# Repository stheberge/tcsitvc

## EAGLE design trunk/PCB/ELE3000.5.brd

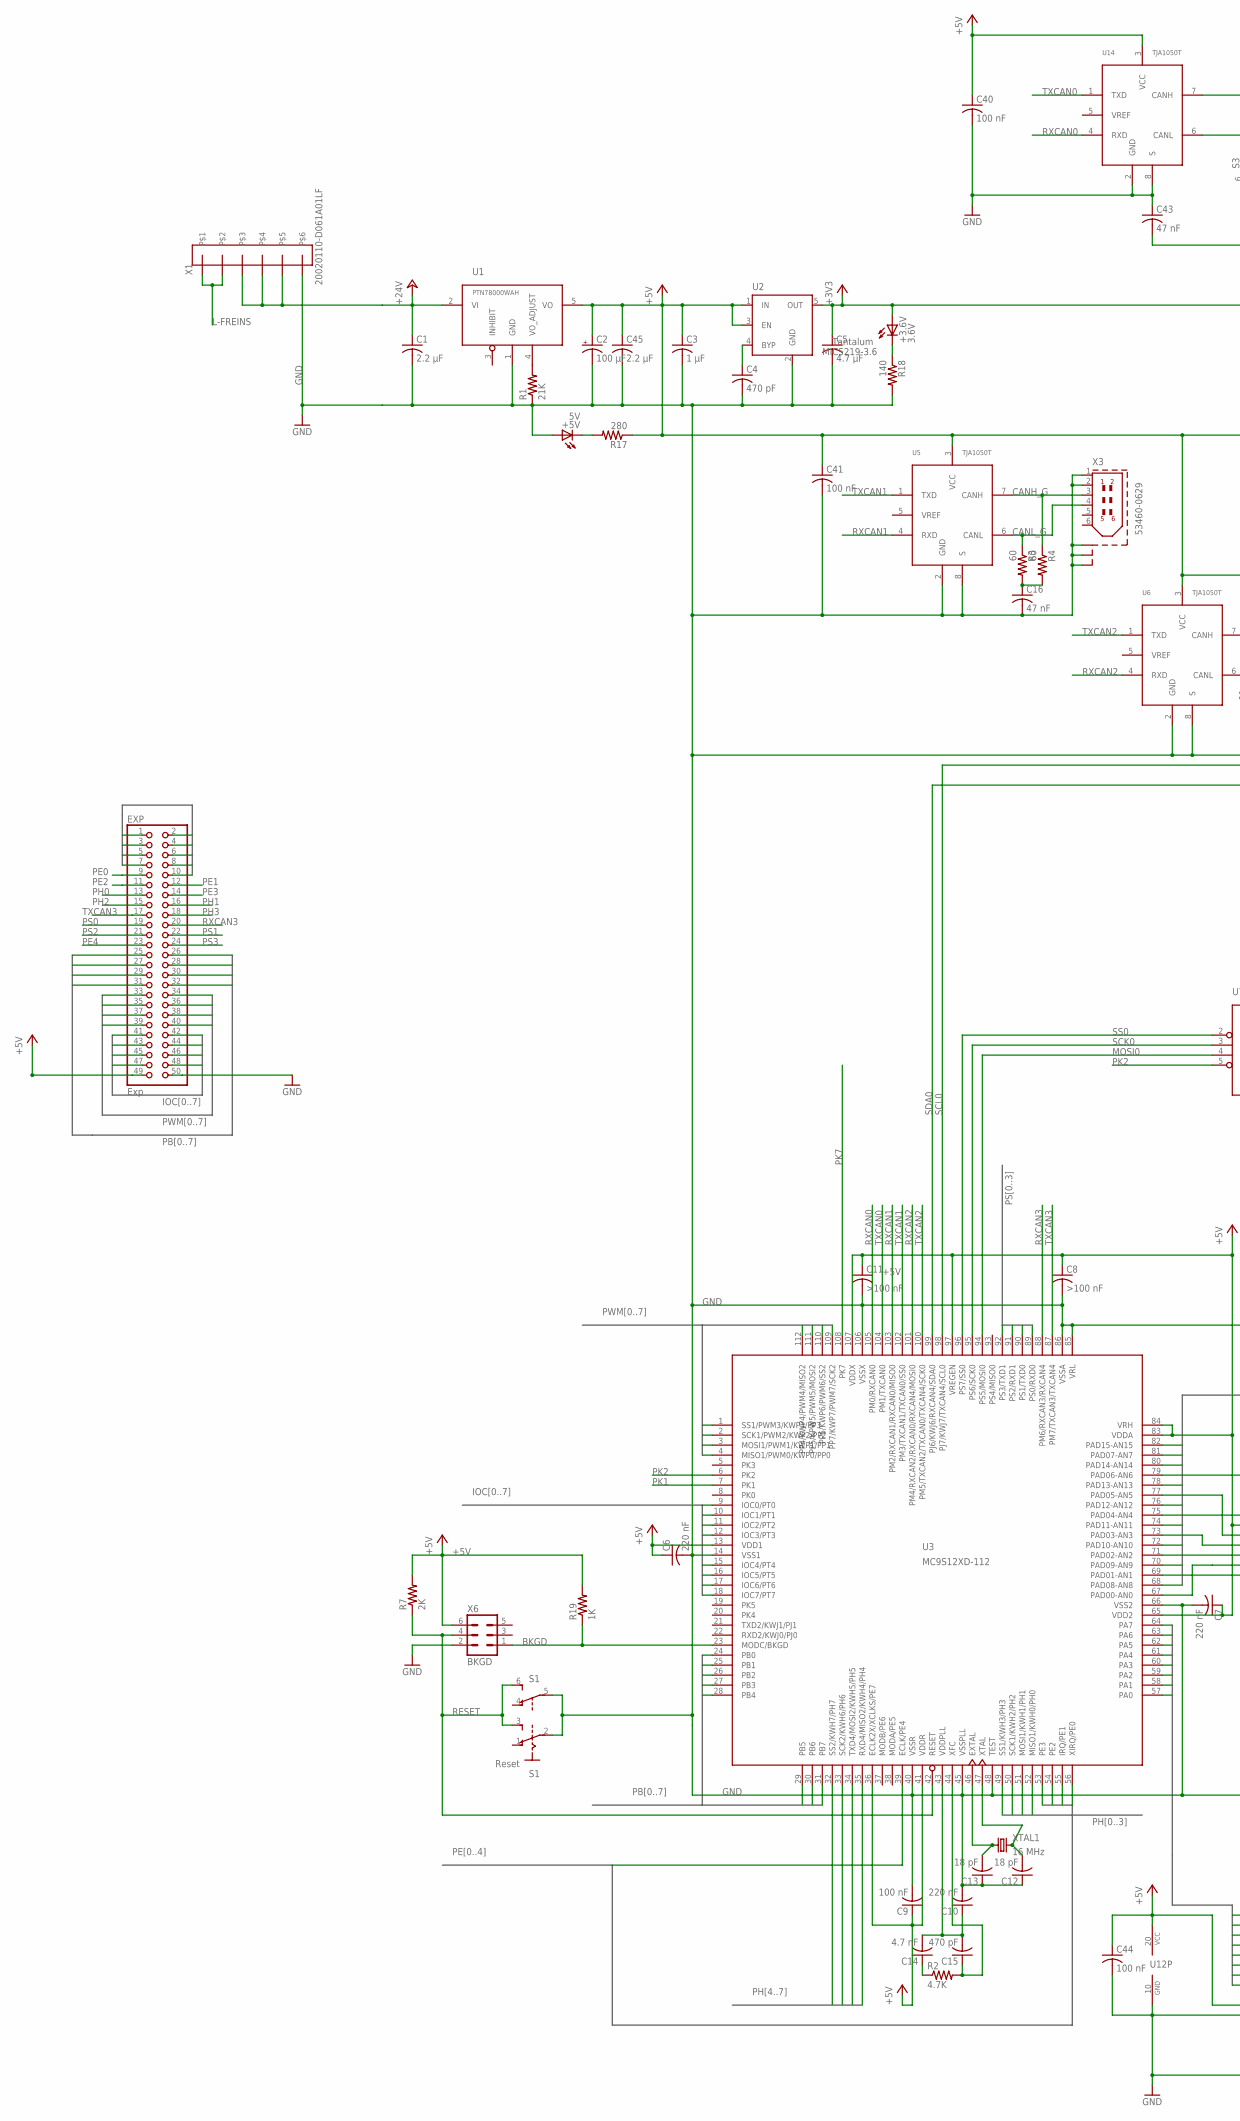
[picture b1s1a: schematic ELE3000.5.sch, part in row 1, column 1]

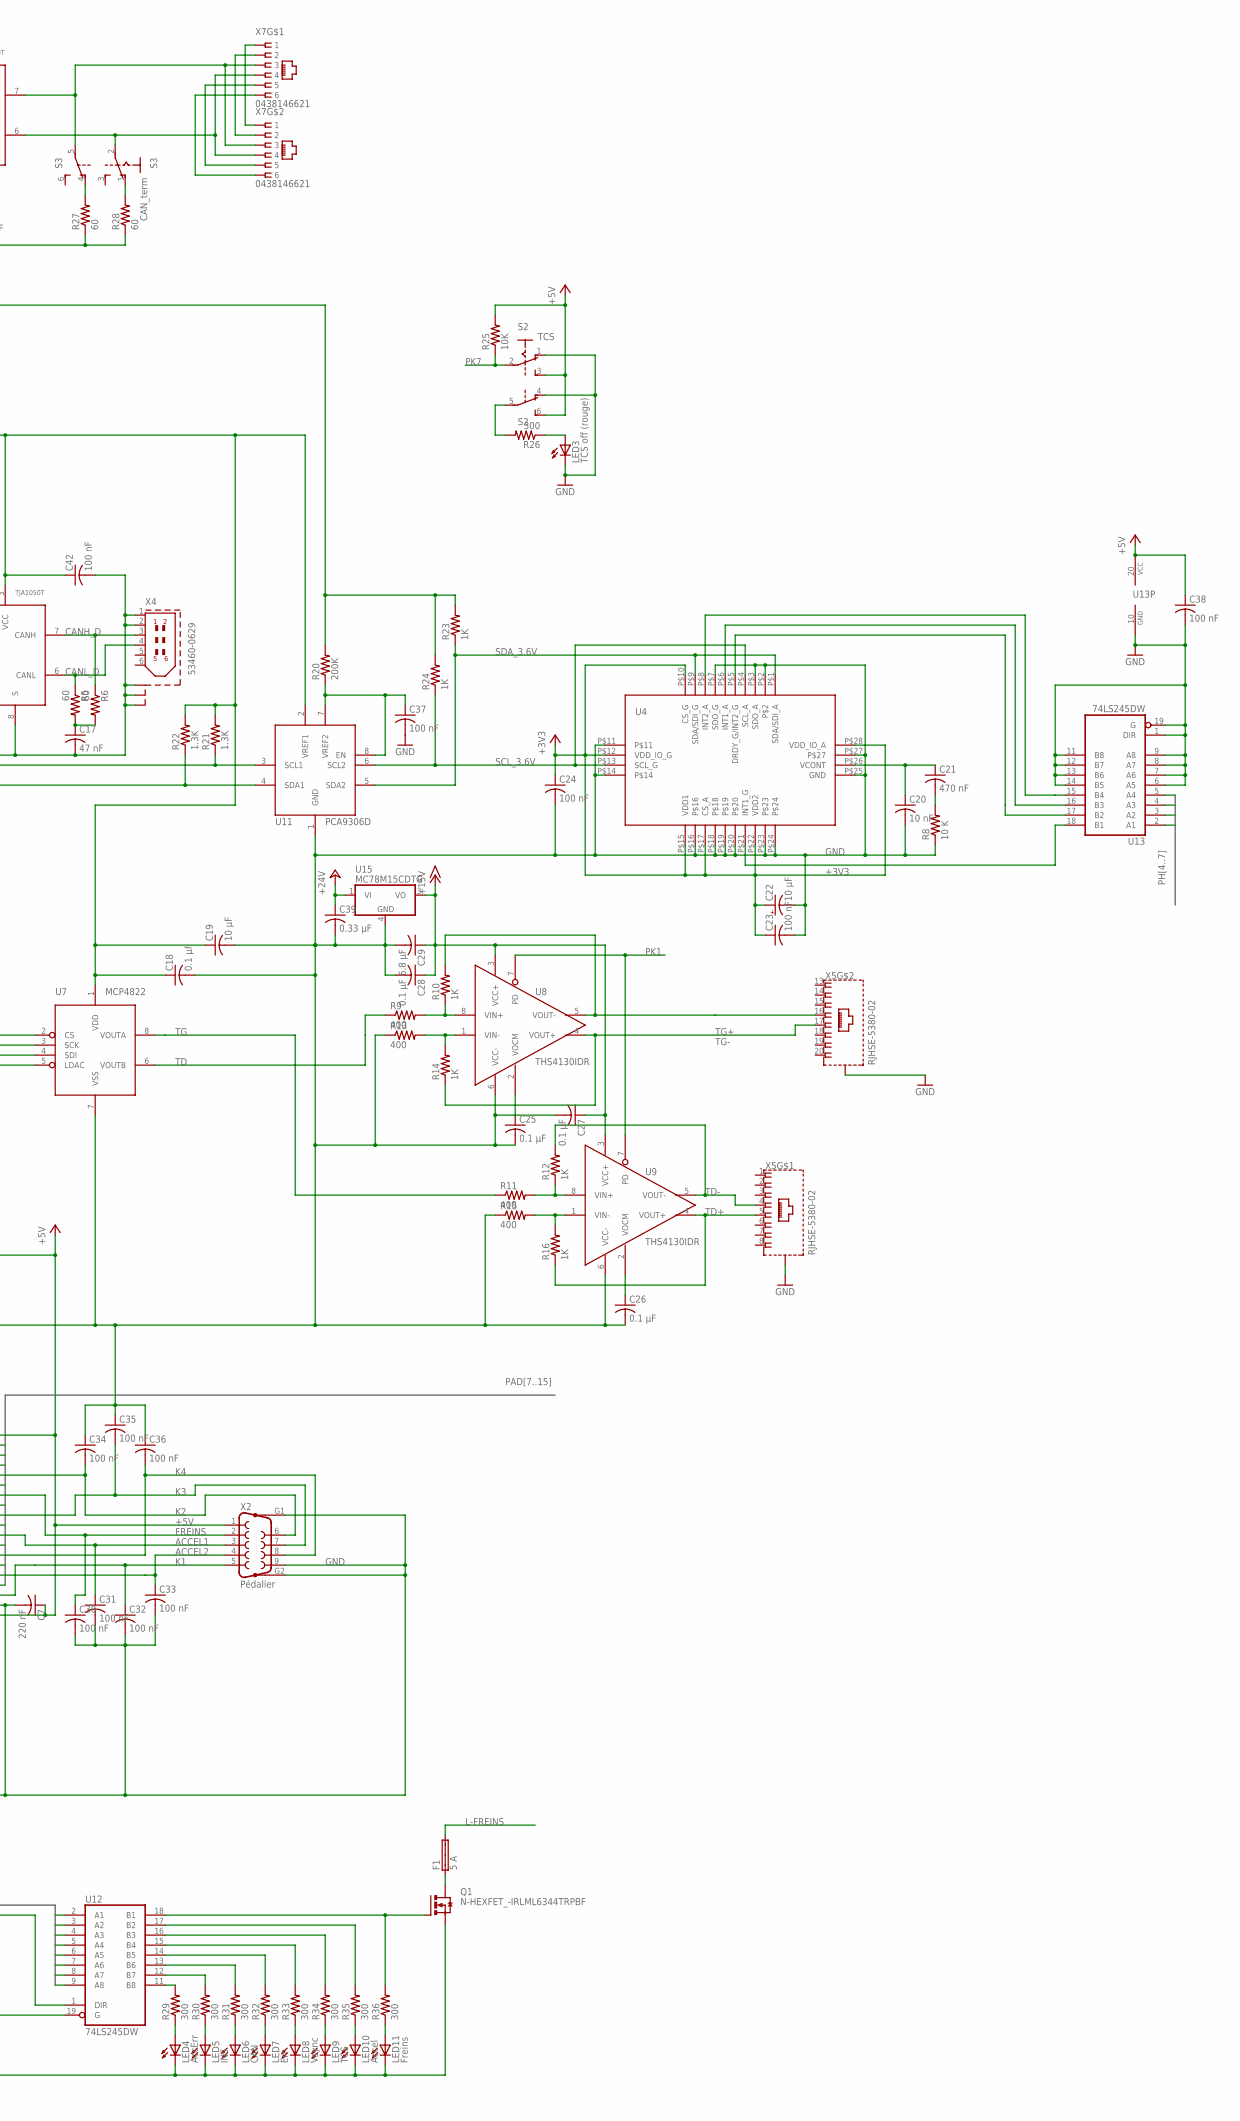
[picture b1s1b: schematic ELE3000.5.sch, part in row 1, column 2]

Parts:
+3.6V: 3.6V; CHIPLED_1206
+5V: 5V; CHIPLED_1206
C1: 2.2 µF; C1206; TOLERANCE ±10%; VOLTAGE 50 V; DIGIKEY 587-2911-1-ND
C2: 100 µF; E2,5-6; VOLTAGE 25V; DIGIKEY 399-6103-ND
C3: 1 µF; C0805; DIGIKEY 490-1692-1-ND
C4: 470 pF; C0805; DIGIKEY 490-1611-1-ND
C5: 4.7 µF; C1206; DIGIKEY 493-2333-1-ND
C6, C7, C10: 220 nF; C0805
C8, C11: >100 nF; C0805
C9, C23, C24, C30, C31, C32, C33, C34, C35, C36, C37, C38, C40, C41, C42, C44: 100 nF; C0805
C12, C13: 18 pF; C0805
C14: 4.7 nF; C0805
C15: 470 pF; C0805
C16, C17, C43: 47 nF; C0805
C18, C25, C26, C27, C28: 0.1 µF; C0805
C19: 10 µF; C1206
C20: 10 nF; C0805
C21: 470 nF; C0805
C22: 10 µF; E2-5
C29: 6.8 µF; C1206
C39: 0.33 µF; C1206
C45: 2.2 µF; C0805; VOLTAGE 25V; DIGIKEY 399-6103-ND
EXP: Exp; 2X25
F1: 5 A; SHK20L
LED3: TCS off (rouge); CHIPLED_1206
LED4: AccErr; CHIPLED_1206
LED5: INS; CHIPLED_1206
LED6: CAN; CHIPLED_1206
LED7: Err; CHIPLED_1206
LED8: Vsync; CHIPLED_1206
LED9: TCS; CHIPLED_1206
LED10: Accel; CHIPLED_1206
LED11: Freins; CHIPLED_1206
Q1: N-HEXFET_-IRLML6344TRPBF; MICRO3
R1: 21K; R0805; TOLERANCE ±1%; DIGIKEY 311-21.0KCRCT-ND
R2: 4.7K; R0805
R3, R4, R5, R6, R27, R28: 60; R1206
R7: 2K; R0805
R8: 10 K; R0805
R9, R11, R13, R15: 400; R0805
R10, R12, R14, R16, R19, R23, R24: 1K; R0805
R17: 280; R0805
R18: 140; R0805
R20: 200K; R0805
R21, R22: 1.3K; R0805
R25: 10K; R0805
R26, R29, R30, R31, R32, R33, R34, R35, R36: 300; R0805
S1: Reset; JS202011CQN
S2: TCS; JS202011CQN
S3: CAN_term; JS202011CQN
U1: PTN78000WAH; EUS
U2: MIC5219-3.6; SOT23-5
U3: MC9S12XD-112; SQFP-S-20X20-112
U4: LSM330DL; LGA-28
U5, U6, U14: TJA1050T; SO08
U7: MCP4822; SO08
U8, U9: THS4130IDR; SO-08
U11: PCA9306D; SO08
U12, U13: 74LS245DW; SO20W
U15: MC78M15CDTG; DPACK_3
X1: 20020110-D061A01LF; 20020110-D061A0
X2: Pédalier; F09HP
X3, X4: 53460-0629
X5: RJHSE-5380-02
X6: BKGD; MA03-2
X7: 0438146621; 2*RJ11
XTAL1: 16 MHz; HC49UP

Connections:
+3V3: +3.6V.A, C5.1, C22.+, C23.1, C24.1, R20.2, R23.2, R24.2, U2.5 (OUT), U4.P$10 (CS_G), U4.P$12 (VDD_IO_G), U4.P$15 (VDD1), U4.P$17 (CS_A), U4.P$22 (VDD2), U4.P$28 (VDD_IO_A)
+5V: C2.+, C3.1, C6.1, C7.1, C8.1, C9.1, C11.1, C18.1, C19.1, C38.1, C40.1, C41.1, C42.1, C44.1, C45.1, EXP.49, R7.2, R17.1, R19.2, R21.2, R22.2, R25.2, S2.3 (S), S2.6 (S), U1.5 (VO), U2.1 (IN), U2.3 (EN), U3.13 (VDD1), U3.36 (ECLK2X/XCLKS/PE7), U3.41 (VDDR), U3.65 (VDD2), U3.83 (VDDA), U3.84 (VRH), U3.97 (VREGEN), U3.107 (VDDX), U5.3 (VCC), U6.3 (VCC), U7.1 (VDD), U11.2 (VREF1), U12.1 (DIR), U12.20 (VCC), U13.20 (VCC), U14.3 (VCC), X2.1, X6.6
+15V: C27.1, C28.1, C29.1, U8.3 (VCC+), U9.3 (VCC+), U15.3 (VO)
+24V: C1.1, C39.1, U1.2 (VI), U15.1 (VI), X1.P$3, X1.P$4, X1.P$5
ACCEL1: C31.1, U3.73 (PAD03-AN3), X2.3
ACCEL2: C33.1, U3.69 (PAD01-AN1), X2.4
BKGD: R19.1, U3.23 (MODC/BKGD), X6.1
CANH_D: R6.1, U6.7 (CANH), X4.3
CANH_G: R4.1, U5.7 (CANH), X3.3
CANL_D: R5.1, U6.6 (CANL), X4.4
CANL_G: R3.1, U5.6 (CANL), X3.4
FREINS: C30.1, U3.77 (PAD05-AN5), X2.2
GND: +5V.A, C1.2, C2.-, C3.2, C4.2, C5.2, C6.2, C7.2, C8.2, C9.2, C10.2, C11.2, C12.1, C13.1, C16.2, C17.2, C18.2, C19.2, C20.2, C22.-, C23.2, C24.2, C25.2, C26.2, C27.2, C28.2, C29.2, C30.2, C31.2, C32.2, C33.2, C34.1, C35.1, C36.1, C37.2, C38.2, C39.2, C40.2, C41.2, C42.2, C43.1, C44.2, C45.2, EXP.50, LED3.C, LED4.C, LED5.C, LED6.C, LED7.C, LED8.C, LED9.C, LED10.C, LED11.C, Q1.2 (S), R1.1, R8.1, R13.1, R15.1, R18.2, S1.2, S1.5, S2.1 (O), S2.4 (O), U1.1 (GND), U2.2 (GND), U3.14 (VSS1), U3.40 (VSSR), U3.45 (VSSPLL), U3.48 (TEST), U3.66 (VSS2), U3.85 (VRL), U3.86 (VSSA), U3.106 (VSSX), U4.P$2, U4.P$3 (SDO_A), U4.P$7 (SDO_G), U4.P$11, U4.P$14, U4.P$16, U4.P$18, U4.P$19, U4.P$20, U4.P$23, U4.P$24, U4.P$25 (GND), U4.P$27, U5.2 (GND), U5.8 (S), U6.2 (GND), U6.8 (S), U7.7 (VSS), U8.6 (VCC-), U9.6 (VCC-), U11.1 (GND), U12.10 (GND), U12.19 (G), U13.1 (DIR), U13.6 (A5), U13.7 (A6), U13.8 (A7), U13.9 (A8), U13.10 (GND), U13.11 (B8), U13.12 (B7), U13.13 (B6), U13.14 (B5), U13.19 (G), U14.2 (GND), U14.8 (S), U15.4 (GND), X1.P$6, X2.9, X2.G1, X2.G2, X3.1, X3.2, X3.S1, X3.S2, X3.S3, X4.1, X4.2, X4.S1, X4.S2, X4.S3, X5.P$1 (S), X5.P$2 (S), X6.2
IOC0: EXP.47, U3.9 (IOC0/PT0)
IOC1: EXP.48, U3.10 (IOC1/PT1)
IOC2: EXP.45, U3.11 (IOC2/PT2)
IOC3: EXP.46, U3.12 (IOC3/PT3)
IOC4: EXP.43, U3.15 (IOC4/PT4)
IOC5: EXP.44, U3.16 (IOC5/PT5)
IOC6: EXP.41, U3.17 (IOC6/PT6)
IOC7: EXP.42, U3.18 (IOC7/PT7)
K1: C32.1, U3.67 (PAD00-AN0), X2.5
K2: C34.2, U3.79 (PAD06-AN6), X2.6
K3: C35.2, U3.75 (PAD04-AN4), X2.7
K4: C36.2, U3.71 (PAD02-AN2), X2.8
L-FREINS: F1.2A, X1.P$1, X1.P$2
MOSI0: U3.94 (PS5/MOSI0), U7.4 (SDI)
unnamed: R1.2, U1.4 (VO_ADJUST)
unnamed: C4.1, U2.4 (BYP)
unnamed: Q1.1 (G), R36.2, U12.18 (B1)
unnamed: U4.P$21 (INT1_G), U13.18 (B1)
unnamed: C12.2, U3.47 (XTAL), XTAL1.2
unnamed: C10.1, C14.2, C15.2, U3.43 (VDDPLL)
unnamed: C14.1, R2.1
unnamed: C15.1, R2.2, U3.44 (XFC)
unnamed: R26.2, S2.5
unnamed: U4.P$5 (DRDY_G/INT2_G), U13.17 (B2)
unnamed: C13.2, U3.46 (EXTAL), XTAL1.1
unnamed: U4.P$6 (INT1_A), U13.16 (B3)
unnamed: U4.P$8 (INT2_A), U13.15 (B4)
unnamed: C17.1, R5.2, R6.2
unnamed: LED3.A, R26.1
unnamed: X7.1, X7.7 (1)
unnamed: F1.1A, Q1.3 (D)
unnamed: C16.1, R3.2, R4.2
unnamed: X7.2, X7.8 (2)
unnamed: S3.5, U14.7 (CANH), X7.3, X7.9 (3)
unnamed: R27.2, S3.4 (O)
unnamed: C20.1, C21.1, U4.P$26 (VCONT)
unnamed: C21.2, R8.2
unnamed: S3.2, U14.6 (CANL), X7.4, X7.10 (4)
unnamed: X7.5, X7.11 (5)
unnamed: X7.6, X7.12 (6)
unnamed: C43.2, R27.1, R28.1
unnamed: R9.2, R10.1, U8.8 (VIN+)
unnamed: R13.2, R14.2, U8.1 (VIN-)
unnamed: +5V.C, R17.2
unnamed: R28.2, S3.1 (O)
unnamed: C26.1, U9.2 (VOCM)
unnamed: C25.1, U8.2 (VOCM)
unnamed: +3.6V.C, R18.1
unnamed: R15.2, R16.2, U9.1 (VIN-)
unnamed: R11.2, R12.1, U9.8 (VIN+)
unnamed: R29.2, U12.11 (B8)
unnamed: R30.2, U12.12 (B7)
unnamed: R31.2, U12.13 (B6)
unnamed: R32.2, U12.14 (B5)
unnamed: R33.2, U12.15 (B4)
unnamed: R34.2, U12.16 (B3)
unnamed: R35.2, U12.17 (B2)
unnamed: LED11.A, R36.1
unnamed: LED10.A, R35.1
unnamed: LED9.A, R34.1
unnamed: LED8.A, R33.1
unnamed: LED7.A, R32.1
unnamed: LED6.A, R31.1
unnamed: LED5.A, R30.1
unnamed: LED4.A, R29.1
PA0: U3.57 (PA0), U12.2 (A1)
PA1: U3.58 (PA1), U12.3 (A2)
PA2: U3.59 (PA2), U12.4 (A3)
PA3: U3.60 (PA3), U12.5 (A4)
PA4: U3.61 (PA4), U12.6 (A5)
PA5: U3.62 (PA5), U12.7 (A6)
PA6: U3.63 (PA6), U12.8 (A7)
PA7: U3.64 (PA7), U12.9 (A8)
PAD7: EXP.1, U3.81 (PAD07-AN7)
PAD8: EXP.10, U3.68 (PAD08-AN8)
PAD9: EXP.7, U3.70 (PAD09-AN9)
PAD10: EXP.8, U3.72 (PAD10-AN10)
PAD11: EXP.5, U3.74 (PAD11-AN11)
PAD12: EXP.6, U3.76 (PAD12-AN12)
PAD13: EXP.3, U3.78 (PAD13-AN13)
PAD14: EXP.4, U3.80 (PAD14-AN14)
PAD15: EXP.2, U3.82 (PAD15-AN15)
PB0: EXP.31, U3.24 (PB0)
PB1: EXP.32, U3.25 (PB1)
PB2: EXP.29, U3.26 (PB2)
PB3: EXP.30, U3.27 (PB3)
PB4: EXP.27, U3.28 (PB4)
PB5: EXP.28, U3.29 (PB5)
PB6: EXP.25, U3.30 (PB6)
PB7: EXP.26, U3.31 (PB7)
PE0: EXP.9, U3.56 (XIRQ/PE0)
PE1: EXP.12, U3.55 (IRQ/PE1)
PE2: EXP.11, U3.54 (PE2)
PE3: EXP.14, U3.53 (PE3)
PE4: EXP.23, U3.39 (ECLK/PE4)
PH0: EXP.13, U3.52 (MISO1/KWH0/PH0)
PH1: EXP.16, U3.51 (MOSI1/KWH1/PH1)
PH2: EXP.15, U3.50 (SCK1/KWH2/PH2)
PH3: EXP.18, U3.49 (SS1/KWH3/PH3)
PH4: U3.35 (RXD4/MISO2/KWH4/PH4), U13.2 (A1)
PH5: U3.34 (TXD4/MOSI2/KWH5/PH5), U13.3 (A2)
PH6: U3.33 (SCK2/KWH6/PH6), U13.4 (A3)
PH7: U3.32 (SS2/KWH7/PH7), U13.5 (A4)
PK1: U3.7 (PK1), U8.7 (PD), U9.7 (PD)
PK2: U3.6 (PK2), U7.5 (LDAC)
PK7: R25.1, S2.2, U3.108 (PK7)
PS0: EXP.19, U3.89 (PS0/RXD0)
PS1: EXP.22, U3.90 (PS1/TXD0)
PS2: EXP.21, U3.91 (PS2/RXD1)
PS3: EXP.24, U3.92 (PS3/TXD1)
PWM0: EXP.33, U3.4 (MISO1/PWM0/KWP0/PP0)
PWM1: EXP.34, U3.3 (MOSI1/PWM1/KWP1/PP1)
PWM2: EXP.35, U3.2 (SCK1/PWM2/KWP2/PP2)
PWM3: EXP.36, U3.1 (SS1/PWM3/KWP3/PP3)
PWM4: EXP.37, U3.112 (PP4/KWP4/PWM4/MISO2)
PWM5: EXP.38, U3.111 (PP5/KPW5/PWM5/MOSI2)
PWM6: EXP.39, U3.110 (PP6/KWP6/PWM6/SS2)
PWM7: EXP.40, U3.109 (PP7/KWP7/PWM7/SCK2)
RESET: R7.1, S1.3 (S), S1.6 (S), U3.42 (RESET), X6.4
RXCAN0: U3.105 (PM0/RXCAN0), U14.4 (RXD)
RXCAN1: U3.103 (PM2/RXCAN1/RXCAN0/MISO0), U5.4 (RXD)
RXCAN2: U3.101 (PM4/RXCAN2/RXCAN0/RXCAN4/MOSI0), U6.4 (RXD)
RXCAN3: EXP.20, U3.88 (PM6/RXCAN3/RXCAN4)
SCK0: U3.95 (PS6/SCK0), U7.3 (SCK)
SCL0: R21.1, U3.98 (PJ7/KWJ7/TXCAN4/SCL0), U11.3 (SCL1)
SCL_3.6V: R24.1, U4.P$4 (SCL_A), U4.P$13 (SCL_G), U11.6 (SCL2)
SDA0: R22.1, U3.99 (PJ6/KWJ6/RXCAN4/SDA0), U11.4 (SDA1)
SDA_3.6V: R23.1, U4.P$1 (SDA/SDI_A), U4.P$9 (SDA/SDI_G), U11.5 (SDA2)
SS0: U3.96 (PS7/SS0), U7.2 (CS)
TD: R11.1, U7.8 (VOUTA)
TD+: R16.1, U9.4 (VOUT+), X5.5
TD-: R12.2, U9.5 (VOUT-), X5.4
TG: R9.1, U7.6 (VOUTB)
TG+: R14.1, U8.4 (VOUT+), X5.17 (5)
TG-: R10.2, U8.5 (VOUT-), X5.16 (4)
TXCAN0: U3.104 (PM1/TXCAN0), U14.1 (TXD)
TXCAN1: U3.102 (PM3/TXCAN1/TXCAN0/SS0), U5.1 (TXD)
TXCAN2: U3.100 (PM5/TXCAN2/TXCAN0/TXCAN4/SCK0), U6.1 (TXD)
TXCAN3: EXP.17, U3.87 (PM7/TXCAN3/TXCAN4)
VREF2: C37.1, R20.1, U11.7 (VREF2), U11.8 (EN)

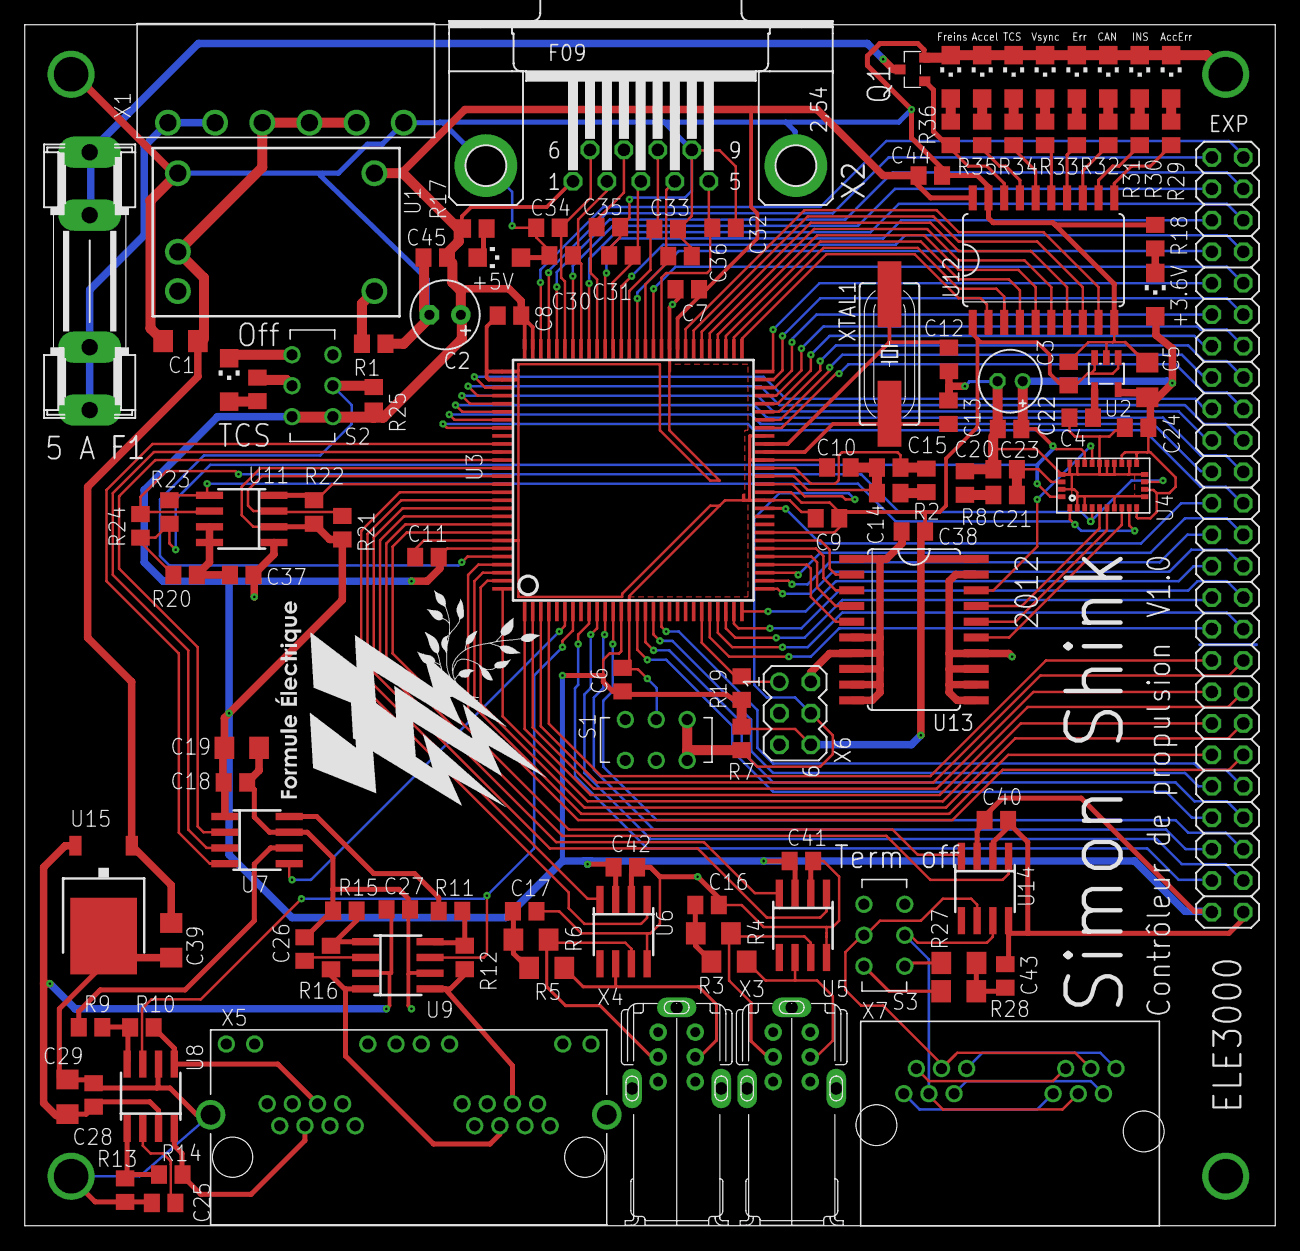
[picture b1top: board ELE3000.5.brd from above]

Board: 2 copper layers, 101.0 x 97.0 mm, 120 parts (0 on the bottom side), 153 nets.

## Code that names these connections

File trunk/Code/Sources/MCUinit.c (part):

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  /* IRQCR: IRQEN=0 */
  IRQCR &= (unsigned char)~(unsigned char)64U;                     
  /* ### Init_GPIO init code */
  /* PORTA: PA7=1,PA6=1,PA5=1,PA4=1,PA3=1,PA2=1,PA1=1,PA0=1 */
  PORTA = 255U;                                      
  /* DDRA: DDRA7=1,DDRA6=1,DDRA5=1,DDRA4=1,DDRA3=1,DDRA2=1,DDRA1=1,DDRA0=1 */
  DDRA = 255U;                                      
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  /* CAN0CTL1: CANE=1,CLKSRC=0,LOOPB=0,LISTEN=1,BORM=0,WUPM=0,SLPAK=0,INITAK=1 */
  CAN0CTL1 = 145U;                                      
  /* ### Init_GPIO init code */
  /* PORTK: PK2=0,PK1=0 */
  PORTK &= (unsigned char)~(unsigned char)6U;                     
  /* PUCR: PUPKE=0 */
  PUCR &= (unsigned char)~(unsigned char)128U;                     
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    
    curFreins = ATD0DR5; //H & ATD0DR0L;
    freins = curFreins + (8-1)*freins;
    freins >>= 3; 
   
    curAccel1 = ATD0DR3; //ATD0DR1; //H & ATD0DR1L;
    accel1 = curAccel1 + (8-1)*accel1;
    accel1 >>= 3; 
    
    curAccel2 = ATD0DR1; //ATD0DR3; //H & ATD0DR2L;
    accel2 = curAccel2 + (8-1)*accel2;
    accel2 >>= 3; 

    //Get accel
    SafetyCheck();
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
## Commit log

2012-09-28 Initial directory structure.
2012-09-28 Initial Release. Code by Simon Shink and Mathieu Provencher. PCB layout by Simon Shink.
2016-03-27 Migrating wiki contents from Google Code

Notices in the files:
trunk/Code/Sources/MCUinit.c:
Copyright : 1997 - 2010 Freescale Semiconductor, Inc. All Rights Reserved.
